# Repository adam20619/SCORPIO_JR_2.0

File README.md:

# SCORPIO_JR_2.0
Second version of the project

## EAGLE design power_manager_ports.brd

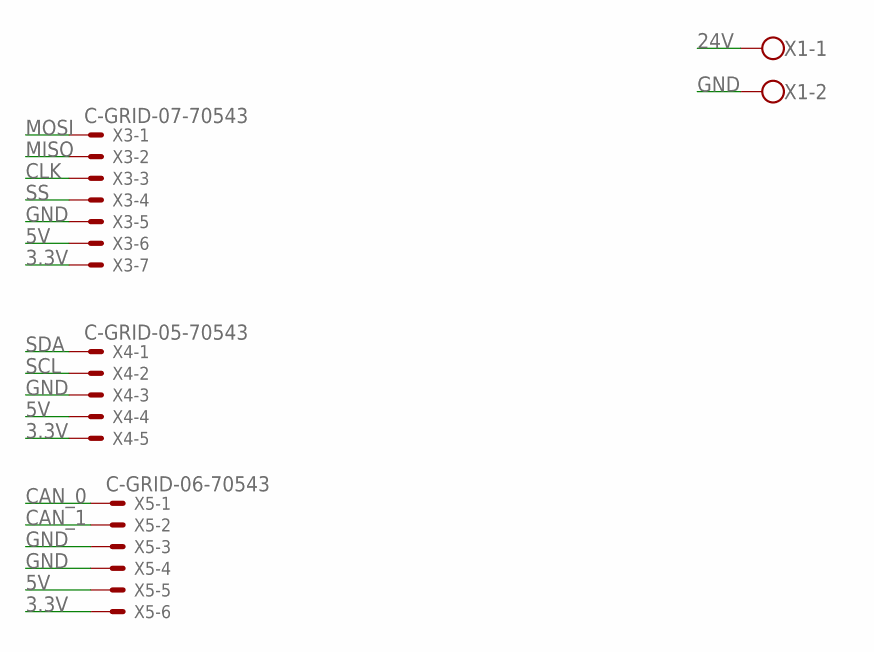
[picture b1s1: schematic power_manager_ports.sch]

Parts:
X1: W239-302
X3: C-GRID-07-70543; 70543-07
X4: C-GRID-05-70543; 70543-05
X5: C-GRID-06-70543; 70543-06

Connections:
3.3V: X3.7, X4.5, X5.6
5V: X3.6, X4.4, X5.5
24V: X1.1
CAN_0: X5.1
CAN_1: X5.2
CLK: X3.3
GND: X1.2, X3.5, X4.3, X5.3, X5.4
MISO: X3.2
MOSI: X3.1
SCL: X4.2
SDA: X4.1
SS: X3.4

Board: 2 copper layers, 4 parts (0 on the bottom side), 3 nets, no tracks yet.

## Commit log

2018-10-13 added basics ports
2018-10-14 New dc_controllers scheme
